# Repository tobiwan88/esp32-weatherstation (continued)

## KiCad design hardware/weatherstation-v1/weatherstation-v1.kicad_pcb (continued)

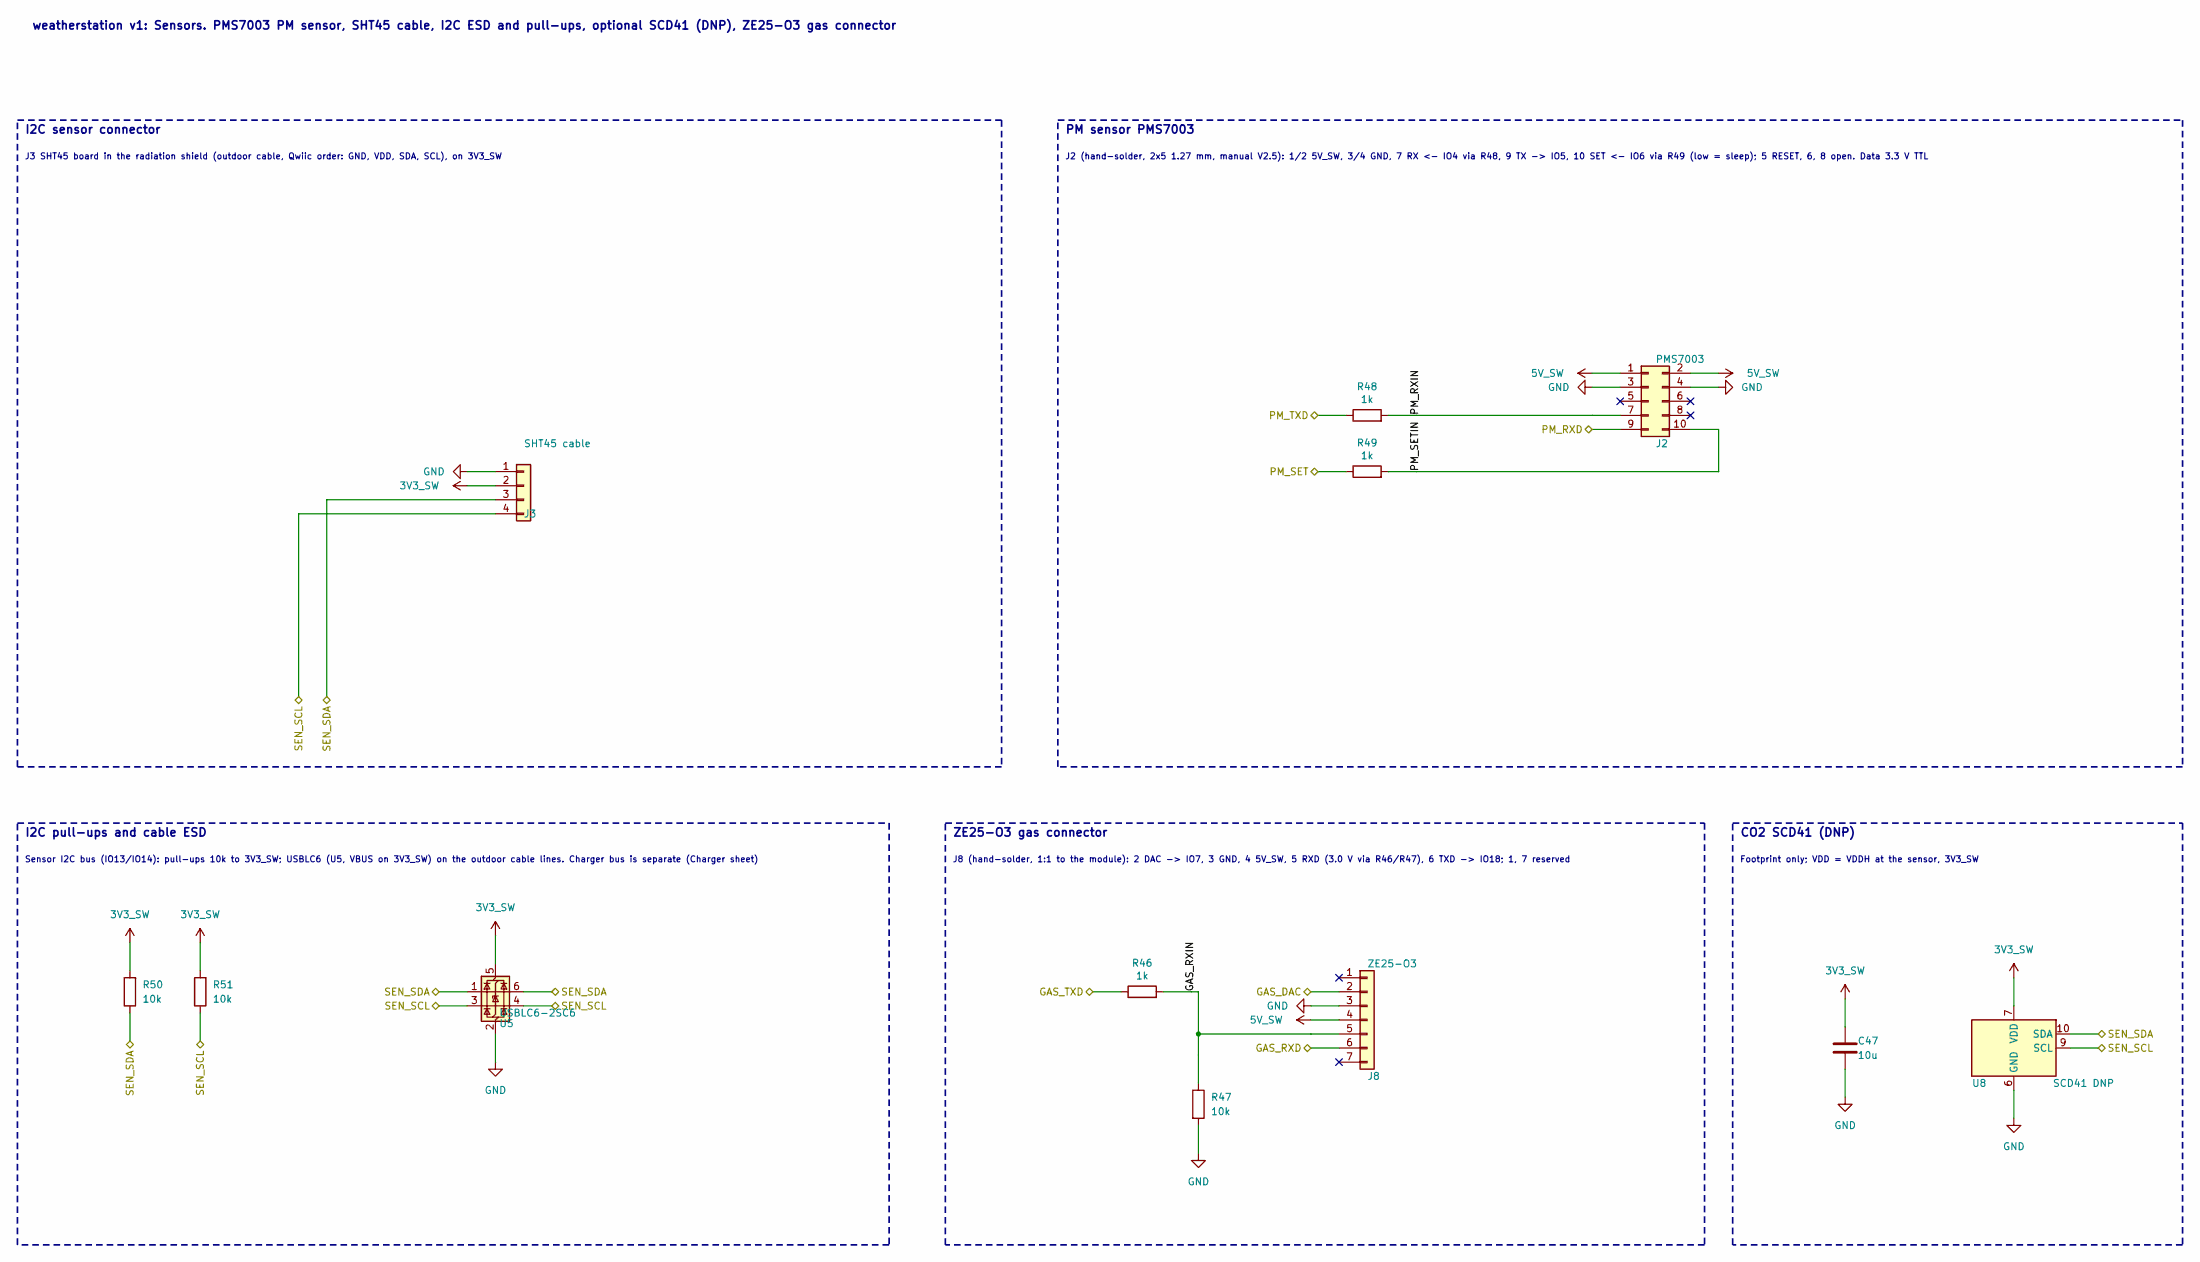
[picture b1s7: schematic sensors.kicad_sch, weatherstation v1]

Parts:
C47: 10u; C_0603_1608Metric; LCSC C19702
J2: PMS7003; PinHeader_2x05_P1.27mm_Vertical
J3: SHT45 cable; JST_SH_SM04B-SRSS-TB_1x04-1MP_P1.00mm_Horizontal; LCSC C160404
J8: ZE25-O3; JST_PH_B7B-PH-K_1x07_P2.00mm_Vertical
R46, R48, R49: 1k; R_0402_1005Metric; LCSC C11702
R47, R50, R51: 10k; R_0402_1005Metric; LCSC C25744
U5: USBLC6-2SC6; SOT-23-6; LCSC C7519
U8: SCD41 DNP; Sensirion_SCD4x-1EP_10.1x10.1mm_P1.25mm_EP4.8x4.8mm

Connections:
3V3_SW: C47.1, J3.2, R50.2, R51.2, U5.5 (VBUS), U8.7 (VDD), U8.19 (VDD); also elsewhere on the board
5V_SW: J2.1, J2.2, J8.4; also elsewhere on the board
/MCU/GAS_DAC: J8.2; also elsewhere on the board
/MCU/GAS_RXD: J8.6; also elsewhere on the board
/MCU/GAS_TXD: R46.1; also elsewhere on the board
/MCU/PM_RXD: J2.9; also elsewhere on the board
/MCU/PM_SET: R49.1; also elsewhere on the board
/MCU/PM_TXD: R48.1; also elsewhere on the board
/MCU/SEN_SCL: J3.4, R51.1, U5.3 (I/O2), U5.4 (I/O2), U8.9 (SCL); also elsewhere on the board
/MCU/SEN_SDA: J3.3, R50.1, U5.1 (I/O1), U5.6 (I/O1), U8.10 (SDA); also elsewhere on the board
/Sensors/GAS_RXIN: J8.5, R46.2, R47.1
/Sensors/PM_RXIN: J2.7, R48.2
/Sensors/PM_SETIN: J2.10, R49.2
GND: C47.2, J2.3, J2.4, J3.1, J8.3, R47.2, U5.2 (GND), U8.6 (GND), U8.20 (GND), U8.21 (GND); also elsewhere on the board

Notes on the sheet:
I2C sensor connector
J3 SHT45 board in the radiation shield (outdoor cable, Qwiic order: GND, VDD, SDA, SCL), on 3V3_SW
PM sensor PMS7003
J2 (hand-solder, 2x5 1.27 mm, manual V2.5): 1/2 5V_SW, 3/4 GND, 7 RX <- IO4 via R48, 9 TX -> IO5, 10 SET <- IO6 via R49 (low = sleep); 5 RESET, 6, 8 open. Data 3.3 V TTL
CO2 SCD41 (DNP)
Footprint only; VDD = VDDH at the sensor, 3V3_SW
I2C pull-ups and cable ESD
Sensor I2C bus (IO13/IO14): pull-ups 10k to 3V3_SW; USBLC6 (U5, VBUS on 3V3_SW) on the outdoor cable lines. Charger bus is separate (Charger sheet)
ZE25-O3 gas connector
J8 (hand-solder, 1:1 to the module): 2 DAC -> IO7, 3 GND, 4 5V_SW, 5 RXD (3.0 V via R46/R47), 6 TXD -> IO18; 1, 7 reserved
weatherstation v1: Sensors. PMS7003 PM sensor, SHT45 cable, I2C ESD and pull-ups, optional SCD41 (DNP), ZE25-O3 gas connector

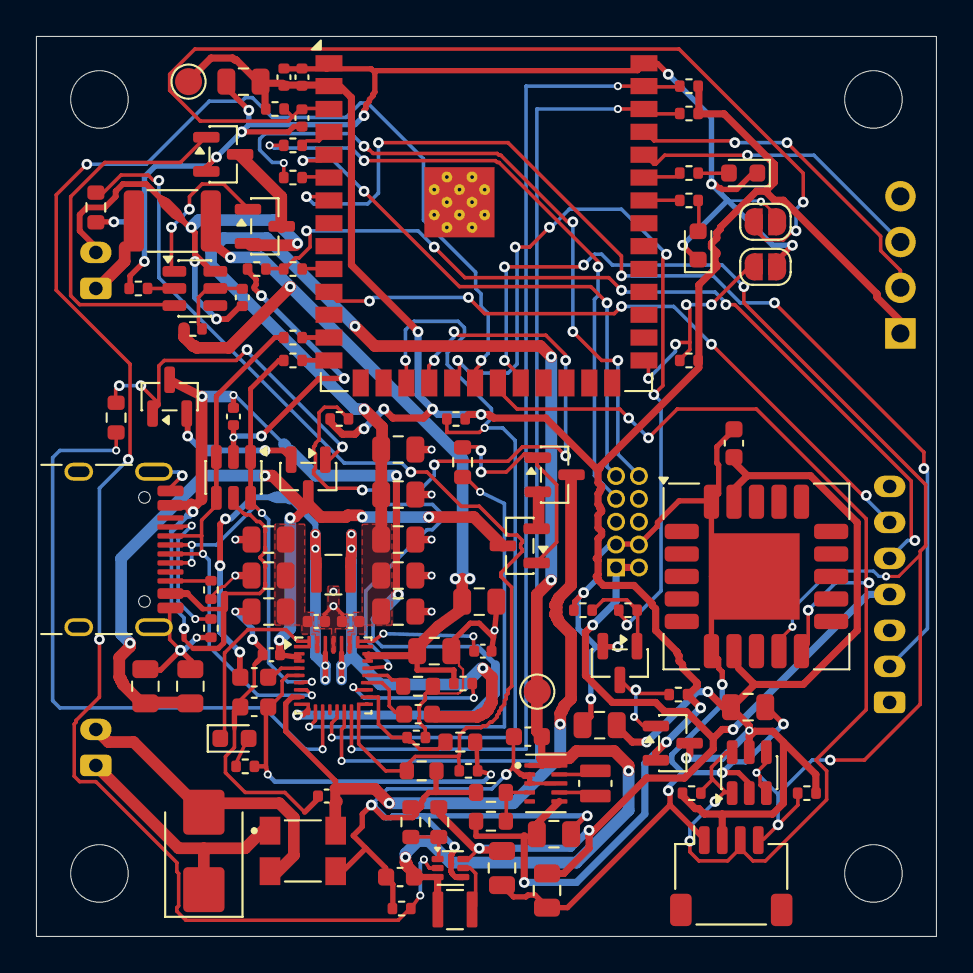
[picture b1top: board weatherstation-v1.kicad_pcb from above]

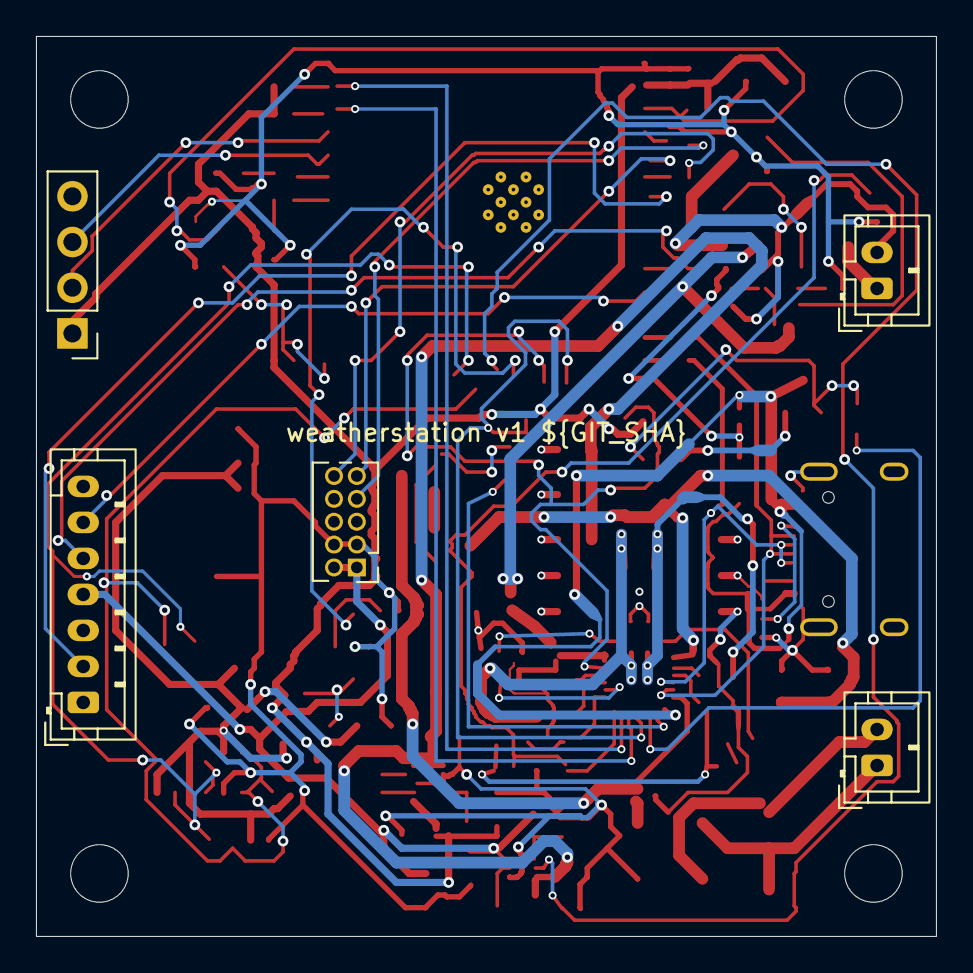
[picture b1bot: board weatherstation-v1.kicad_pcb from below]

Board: 4 copper layers, 50.0 x 50.0 mm, 112 parts (5 on the bottom side), 75 nets.

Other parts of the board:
H1, H2, H3, H4: MountingHole_3.2mm_M3_ISO7380

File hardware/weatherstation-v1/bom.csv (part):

Comment,Designator,Footprint,Quantity,LCSC Part #,Class,Status,Function / notes
USB-C,J1,Connector_USB:USB_C_Receptacle_HRO_TYPE-C-31-M-12,1,C165948,Extended,VERIFIED LCSC part (class and stock 2026-10-31; datasheet values open),
USBLC6-2SC6,"U4,U5",Package_TO_SOT_SMD:SOT-23-6,2,C7519,Extended,VERIFIED LCSC part (class and stock 2026-10-31; datasheet values open),U4: USBLC6-2SC6 (USB); U5: USBLC6-2SC6 (I2C)
5.1k,"R9,R10,R17",Resistor_SMD:R_0402_1005Metric,3,C25905,Basic,VERIFIED LCSC part (class and stock 2026-10-31; datasheet values open),R17: 5.1k (TS top; thresholds about +0.9 C vs 5.24k/30.31k)
AO3400A,"M1,M2,M3,M4,M60,M61",Package_TO_SOT_SMD:SOT-23,6,C20917,Basic,VERIFIED LCSC part (class and stock 2026-10-31; datasheet values open),"M1: AO3400A ACFET1 (N-channel, BQ25798 back-to-back); M2: AO3400A RBFET1 (N-channel, BQ25798 back-to-back); M3: AO3400A ACFET2 (N-channel, BQ25798 back-to-back); M4: AO3400A RBFET2 (N-channel, BQ25798 back-to-back); M60: AO3400A discharge FET (OD); M61: AO3400A charge FET (OC)"
300,"R11,R12",Resistor_SMD:R_0603_1608Metric,2,C23025,Basic,VERIFIED LCSC part (class and stock 2026-10-31; datasheet values open),R11: 300 (candidate; figure 294); R12: 300 (candidate; figure 294)
0.1u,"C1,C2,C6,C9,C13,C31,C60",Capacitor_SMD:C_0402_1005Metric,7,C307331,Basic,VERIFIED LCSC part (class and stock 2026-10-31; datasheet values open),C31: 100n; C60: 0.1u (HY2112 VDD)
SMBJ10A,D1,Diode_SMD:D_SMB,1,C151250,Extended,VERIFIED LCSC part (class and stock 2026-10-31; datasheet values open),"D1: SMBJ10A (PV surge, standoff 10 V, clamp 17 V)"
CMC 90R 3A,L3,weatherstation:CMF4532F_4P,1,C963746,Extended,VERIFIED LCSC part (class and stock 2026-10-31; datasheet values open),L3: CM choke 90 ohm 3 A (CMF4532F-900-2P-T; datasheet page to confirm)
PV IN,J5,Connector_JST:JST_PH_B2B-PH-K_1x02_P2.00mm_Vertical,1,n/a,n/a,HAND-SOLDER,
BQ25798RQMR,U3,Package_DFN_QFN:Texas_RQM0029A_VQFN-29_4x4mm_P0.4mm,1,C2876593,Extended,VERIFIED LCSC part (class and stock 2026-10-31; datasheet values open),
1uH,"L1,L5",weatherstation:L_TDK_VLS252010,2,C88211,Extended,VERIFIED LCSC part (class and stock 2026-10-31; datasheet values open),"L1: 1uH (TDK VLS252010HBX-1R0M-1: Isat 3.22 A, Itemp 2.55 A, 65 mohm max); L5: 1uH (VLS252010HBX-1R0M-1, same as L1)"
PTC 3A,F1,Fuse:Fuse_1812_4532Metric,1,C21004,Extended,VERIFIED LCSC part (class and stock 2026-10-31; datasheet values open),F1: PTC 3 A hold (SMD1812P300TF)
47n,"C3,C4",Capacitor_SMD:C_0603_1608Metric,2,C1622,Basic,VERIFIED LCSC part (class and stock 2026-10-31; datasheet values open),
4.7u,C5,Capacitor_SMD:C_0603_1608Metric,1,C19666,Basic,VERIFIED LCSC part (class and stock 2026-10-31; datasheet values open),
10u,"C7,C8,C10,C11,C12,C14,C15,C16,C17,C18,C19,C20",Capacitor_SMD:C_0805_2012Metric,12,C15850,Basic,VERIFIED LCSC part (class and stock 2026-10-31; datasheet values open),
1n,C21,Capacitor_SMD:C_0402_1005Metric,1,C1523,Basic,VERIFIED LCSC part (class and stock 2026-10-31; datasheet values open),
100,"R13,R60",Resistor_SMD:R_0402_1005Metric,2,C25076,Basic,VERIFIED LCSC part (class and stock 2026-10-31; datasheet values open),R60: 100 (HY2112 VDD)
3.0k,R14,Resistor_SMD:R_0603_1608Metric,1,C4211,Basic,VERIFIED LCSC part (class and stock 2026-10-31; datasheet values open),"R14: 3.0k (PROG: 1S, 1.5 MHz)"
120k,R15,Resistor_SMD:R_0603_1608Metric,1,C25808,Basic,VERIFIED LCSC part (class and stock 2026-10-31; datasheet values open),R15: 120k (ILIM: REGN 5 V x 100/220 = 2.27 V -> 1.59 A clamp)
100k,"R16,R20,R40,R42,R45",Resistor_SMD:R_0402_1005Metric,5,C25741,Basic,VERIFIED LCSC part (class and stock 2026-10-31; datasheet values open),R45: 100k (EN pull-down: boost off by default)
30k,R18,Resistor_SMD:R_0603_1608Metric,1,C22984,Basic,VERIFIED LCSC part (class and stock 2026-10-31; datasheet values open),R18: 30k (TS bottom)
2.2k,R19,Resistor_SMD:R_0402_1005Metric,1,C25879,Basic,VERIFIED LCSC part (class and stock 2026-10-31; datasheet values open),
STAT red,"D2,D10,D11",LED_SMD:LED_0603_1608Metric,3,C2286,Basic,VERIFIED LCSC part (class and stock 2026-10-31; datasheet values open),D10: LED1 red; D11: LED2 red
10k,"R22,R30,R31,R47,R50,R51,R54,R55",Resistor_SMD:R_0402_1005Metric,8,C25744,Basic,VERIFIED LCSC part (class and stock 2026-10-31; datasheet values open),
BATTERY,J6,Connector_JST:JST_PH_B2B-PH-K_1x02_P2.00mm_Vertical,1,n/a,n/a,HAND-SOLDER,
10k NTC,TH1,Resistor_SMD:R_0603_1608Metric,1,C13564,Extended,VERIFIED LCSC part (class and stock 2026-10-31; datasheet values open),"TH1: 10k NTC NCP18XH103F03RB (TS, next to J6)"
HY2112-CB,U6,Package_TO_SOT_SMD:SOT-23-6,1,C168764,Extended,VERIFIED LCSC part (class and stock 2026-10-31; datasheet values open),U6: HY2112-CB LiFePO4 protection
2k,R61,Resistor_SMD:R_0402_1005Metric,1,C4109,Basic,VERIFIED LCSC part (class and stock 2026-10-31; datasheet values open),R61: 2k (HY2112 CS)
ESP32-S3-WROOM-1-N8,U1,RF_Module:ESP32-S3-WROOM-1,1,C2913198,Extended,VERIFIED LCSC part (class and stock 2026-10-31; datasheet values open),
22u,"C30,C41,C42,C43,C45,C46",Capacitor_SMD:C_0805_2012Metric,6,C45783,Basic,VERIFIED LCSC part (class and stock 2026-10-31; datasheet values open),C41: 22u (TPS63802 output: 22 uF per table 10-1); C45: 22u (boost output); C46: 22u (boost output)
1u,"C32,C33",Capacitor_SMD:C_0402_1005Metric,2,C52923,Basic,VERIFIED LCSC part (class and stock 2026-10-31; datasheet values open),
RESET,JP1,Jumper:SolderJumper-2_P1.3mm_Open_RoundedPad1.0x1.5mm,1,n/a,n/a,NOT ASSEMBLED,
BOOT,JP2,Jumper:SolderJumper-2_P1.3mm_Open_RoundedPad1.0x1.5mm,1,n/a,n/a,NOT ASSEMBLED,
22,"R32,R33",Resistor_SMD:R_0402_1005Metric,2,C25092,Basic,VERIFIED LCSC part (class and stock 2026-10-31; datasheet values open),
1k,"R34,R35,R41,R46,R48,R49",Resistor_SMD:R_0402_1005Metric,6,C11702,Basic,VERIFIED LCSC part (class and stock 2026-10-31; datasheet values open),R46: 1k (GAS RXD level: 3.3 V x 10/11 = 3.0 V); R48: 1k (PM RX series); R49: 1k (PM SET series)
DEBUG UART,J7,Connector_PinHeader_2.54mm:PinHeader_1x04_P2.54mm_Vertical,1,n/a,n/a,HAND-SOLDER,
TPS63802,U2,weatherstation:TPS63802_DLA_VSON-HR-10_2x3mm,1,C2845237,Extended,VERIFIED LCSC part (class and stock 2026-10-31; datasheet values open),U2: TPS63802DLA 3.3 V buck-boost
0.47uH,L4,weatherstation:L_Sunlord_WPN201610H,1,C97009,Extended,VERIFIED LCSC part (class and stock 2026-10-31; datasheet values open),"L4: 0.47uH (Sunlord WPN201610HR47MT: Isat 4.0 A max, Irms 2.7 A)"
220k 1%,R52,Resistor_SMD:R_0603_1608Metric,1,C22961,Basic,VERIFIED LCSC part (class and stock 2026-10-31; datasheet values open),R52: 220k 1% (FB top: 0.5 V x (1 + 220k/39k) = 3.32 V)
39k 1%,R53,Resistor_SMD:R_0603_1608Metric,1,C23153,Basic,VERIFIED LCSC part (class and stock 2026-10-31; datasheet values open),"R53: 39k 1% (FB bottom, datasheet max 100k)"
10u,"C40,C44,C47",Capacitor_SMD:C_0603_1608Metric,3,C19702,Basic,VERIFIED LCSC part (class and stock 2026-10-31; datasheet values open),C44: 10u (boost input); C47: 10u (SCD41 VDD)
AO3401A,Q40,Package_TO_SOT_SMD:SOT-23,1,C15127,Basic,VERIFIED LCSC part (class and stock 2026-10-31; datasheet values open),Q40: AO3401A 3V3_SW switch
2N7002,Q41,Package_TO_SOT_SMD:SOT-23,1,C8545,Basic,VERIFIED LCSC part (class and stock 2026-10-31; datasheet values open),Q41: 2N7002 (sensor enable)
TPS61023,U7,Package_TO_SOT_SMD:SOT-563,1,C919459,Extended,VERIFIED LCSC part (class and stock 2026-10-31; datasheet values open),U7: TPS61023DRLR 5 V boost
510k 1%,R43,Resistor_SMD:R_0603_1608Metric,1,C23192,Basic,VERIFIED LCSC part (class and stock 2026-10-31; datasheet values open),R43: 510k 1% (boost FB top: 0.595 V x (1 + 510k/68k) = 5.06 V)
68k 1%,R44,Resistor_SMD:R_0603_1608Metric,1,C23231,Basic,VERIFIED LCSC part (class and stock 2026-10-31; datasheet values open),R44: 68k 1% (boost FB bottom)
PMS7003,J2,Connector_PinHeader_1.27mm:PinHeader_2x05_P1.27mm_Vertical,1,n/a,n/a,HAND-SOLDER,J2: PMS7003 (2x5 1.27 mm)
SCD41 DNP,U8,Sensor:Sensirion_SCD4x-1EP_10.1x10.1mm_P1.25mm_EP4.8x4.8mm,1,n/a,n/a,NOT ASSEMBLED,U8: SCD41 DNP (C3659294)
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
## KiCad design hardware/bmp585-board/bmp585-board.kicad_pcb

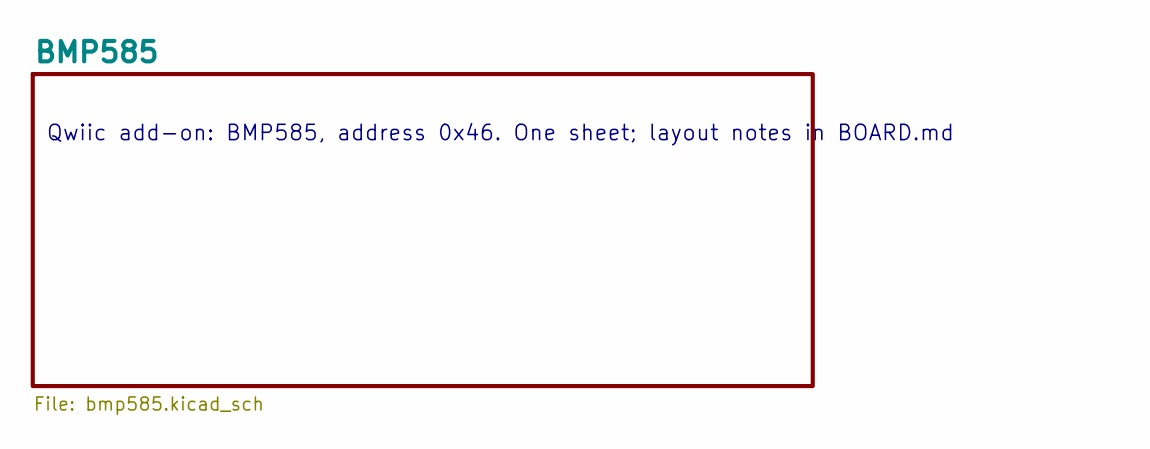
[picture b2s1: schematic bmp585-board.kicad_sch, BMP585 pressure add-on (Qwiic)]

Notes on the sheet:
Qwiic add-on: BMP585, address 0x46. One sheet; layout notes in BOARD.md

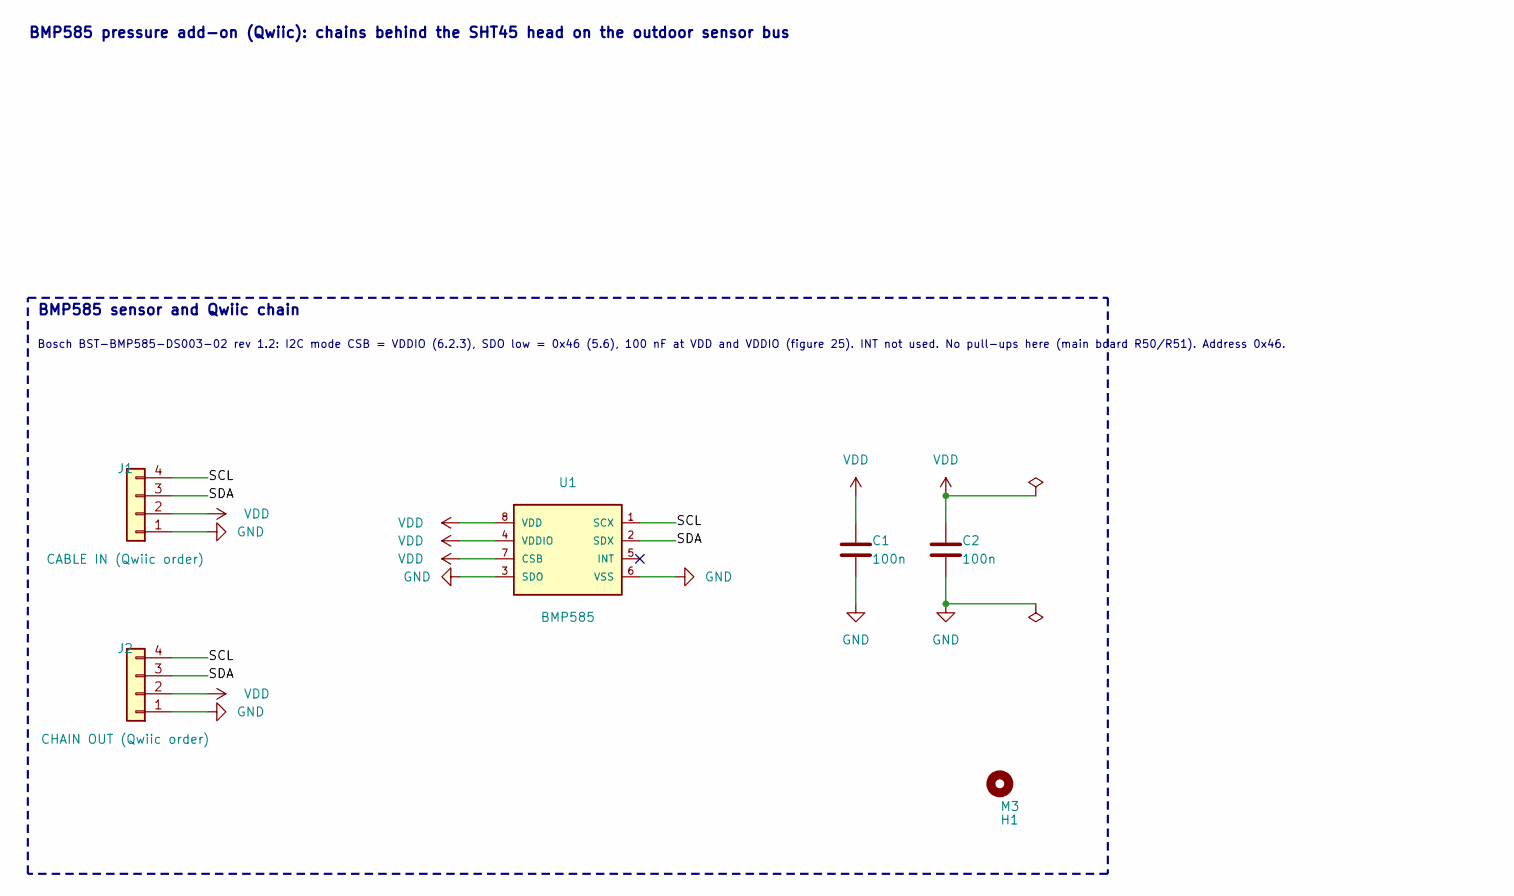
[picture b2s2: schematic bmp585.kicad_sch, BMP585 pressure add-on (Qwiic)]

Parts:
C1, C2: 100n; C_0603_1608Metric; LCSC C14663
H1: M3; MountingHole_3.2mm_M3
J1: CABLE IN (Qwiic order); JST_SH_SM04B-SRSS-TB_1x04-1MP_P1.00mm_Horizontal; LCSC C160404
J2: CHAIN OUT (Qwiic order); JST_SH_SM04B-SRSS-TB_1x04-1MP_P1.00mm_Horizontal; LCSC C160404
U1: BMP585; BMP585_LGA-8_3.25x3.25mm; LCSC C18184976

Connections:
/BMP585/SCL: J1.4, J2.4, U1.1 (SCX)
/BMP585/SDA: J1.3, J2.3, U1.2 (SDX)
GND: C1.2, C2.2, J1.1, J2.1, U1.3 (SDO), U1.6 (VSS)
VDD: C1.1, C2.1, J1.2, J2.2, U1.4 (VDDIO), U1.7 (CSB), U1.8 (VDD)

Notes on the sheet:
BMP585 sensor and Qwiic chain
Bosch BST-BMP585-DS003-02 rev 1.2: I2C mode CSB = VDDIO (6.2.3), SDO low = 0x46 (5.6), 100 nF at VDD and VDDIO (figure 25). INT not used. No pull-ups here (main board R50/R51). Address 0x46.
BMP585 pressure add-on (Qwiic): chains behind the SHT45 head on the outdoor sensor bus

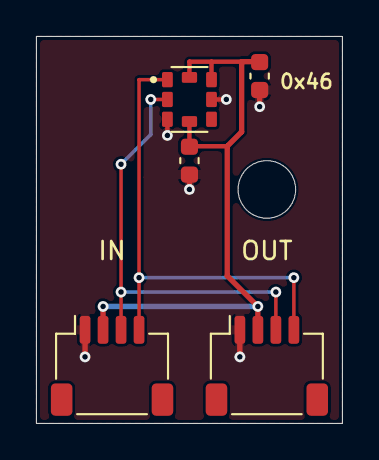
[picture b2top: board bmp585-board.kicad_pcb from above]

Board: 2 copper layers, 17.0 x 21.5 mm, 6 parts (0 on the bottom side), 4 nets.

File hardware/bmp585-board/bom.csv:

Comment,Designator,Footprint,Quantity,LCSC Part #,Class
BMP585,U1,weatherstation:BMP585_LGA-8_3.25x3.25mm,1,C18184976,Extended
100n,C1,Capacitor_SMD:C_0603_1608Metric,1,C14663,Basic
100n,C2,Capacitor_SMD:C_0603_1608Metric,1,C14663,Basic
CABLE IN (Qwiic order),J1,Connector_JST:JST_SH_SM04B-SRSS-TB_1x04-1MP_P1.00mm_Horizontal,1,C160404,Extended
CHAIN OUT (Qwiic order),J2,Connector_JST:JST_SH_SM04B-SRSS-TB_1x04-1MP_P1.00mm_Horizontal,1,C160404,Extended

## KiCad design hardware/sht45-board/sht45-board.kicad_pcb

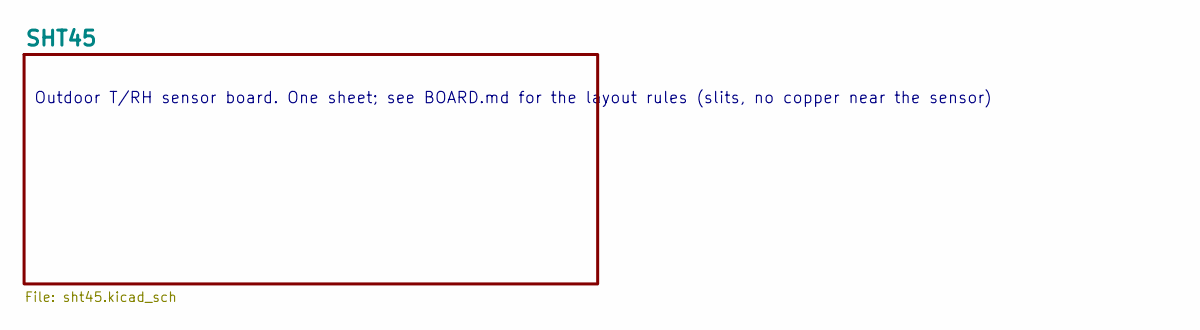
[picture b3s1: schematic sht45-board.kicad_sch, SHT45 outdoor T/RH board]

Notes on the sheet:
Outdoor T/RH sensor board. One sheet; see BOARD.md for the layout rules (slits, no copper near the sensor)

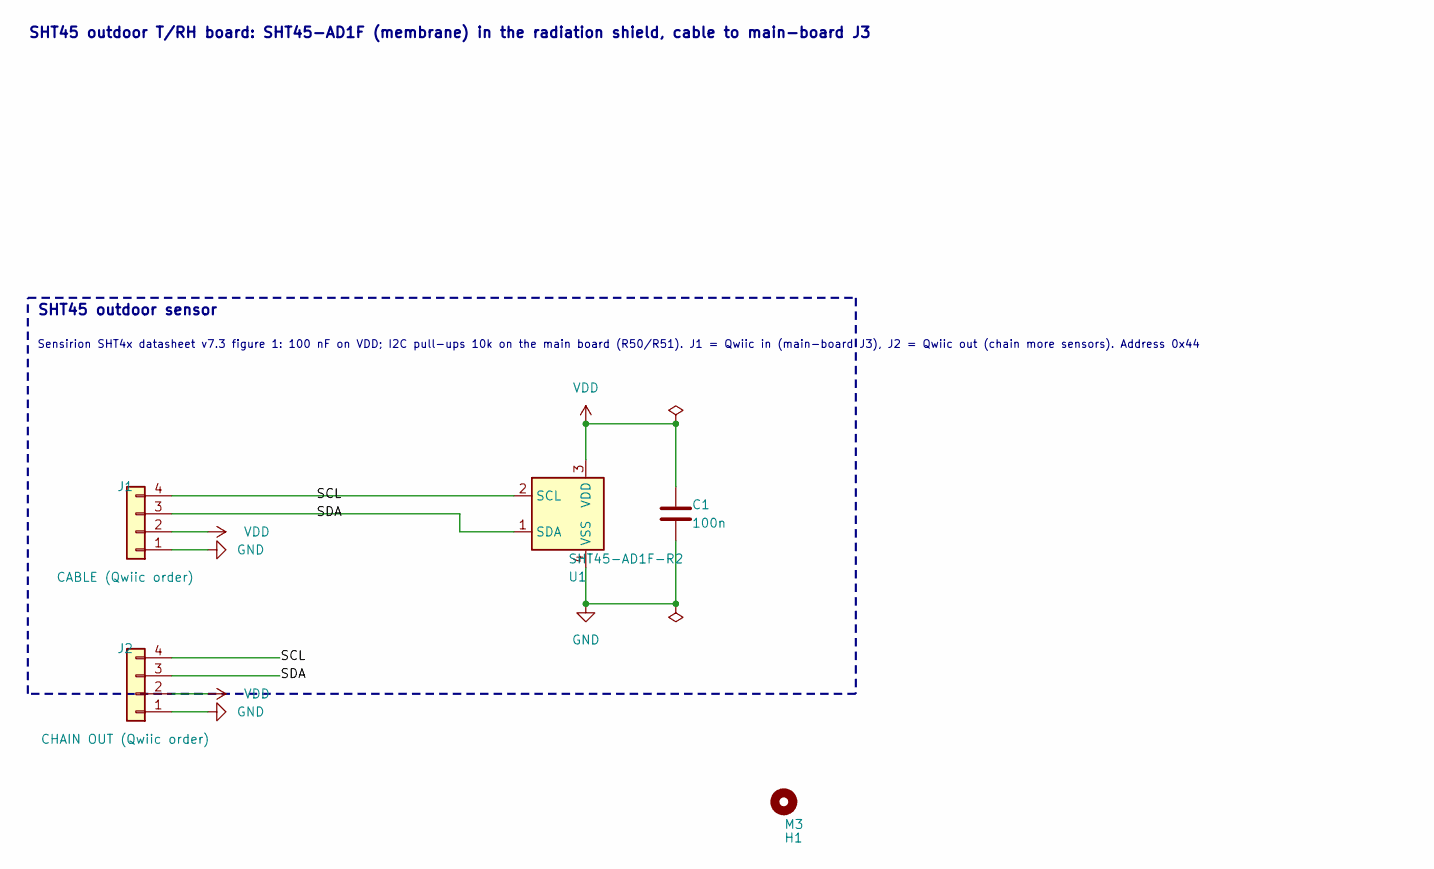
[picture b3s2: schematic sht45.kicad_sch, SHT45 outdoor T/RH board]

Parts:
C1: 100n; C_0603_1608Metric; LCSC C14663
H1: M3; MountingHole_3.2mm_M3
J1: CABLE (Qwiic order); JST_SH_SM04B-SRSS-TB_1x04-1MP_P1.00mm_Horizontal; LCSC C160404
J2: CHAIN OUT (Qwiic order); JST_SH_SM04B-SRSS-TB_1x04-1MP_P1.00mm_Horizontal; LCSC C160404
U1: SHT45-AD1F-R2; Sensirion_DFN-4_1.5x1.5mm_P0.8mm_SHT4x_NoCentralPad; LCSC C5360602

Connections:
/SHT45/SCL: J1.4, J2.4, U1.2 (SCL)
/SHT45/SDA: J1.3, J2.3, U1.1 (SDA)
GND: C1.2, J1.1, J2.1, U1.4 (VSS)
VDD: C1.1, J1.2, J2.2, U1.3 (VDD)

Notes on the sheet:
SHT45 outdoor sensor
Sensirion SHT4x datasheet v7.3 figure 1: 100 nF on VDD; I2C pull-ups 10k on the main board (R50/R51). J1 = Qwiic in (main-board J3), J2 = Qwiic out (chain more sensors). Address 0x44
SHT45 outdoor T/RH board: SHT45-AD1F (membrane) in the radiation shield, cable to main-board J3

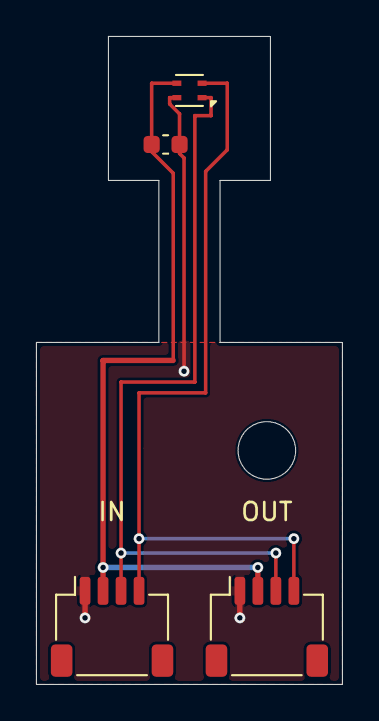
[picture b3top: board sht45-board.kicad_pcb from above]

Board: 2 copper layers, 17.0 x 36.0 mm, 5 parts (0 on the bottom side), 4 nets.

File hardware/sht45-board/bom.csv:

Comment,Designator,Footprint,Quantity,LCSC Part #,Class
SHT45-AD1F-R2,U1,Sensor_Humidity:Sensirion_DFN-4_1.5x1.5mm_P0.8mm_SHT4x_NoCentralPad,1,C5360602,Extended
100n,C1,Capacitor_SMD:C_0603_1608Metric,1,C14663,Basic
CABLE (Qwiic order),J1,Connector_JST:JST_SH_SM04B-SRSS-TB_1x04-1MP_P1.00mm_Horizontal,1,C160404,Extended
CHAIN OUT (Qwiic order),J2,Connector_JST:JST_SH_SM04B-SRSS-TB_1x04-1MP_P1.00mm_Horizontal,1,C160404,Extended

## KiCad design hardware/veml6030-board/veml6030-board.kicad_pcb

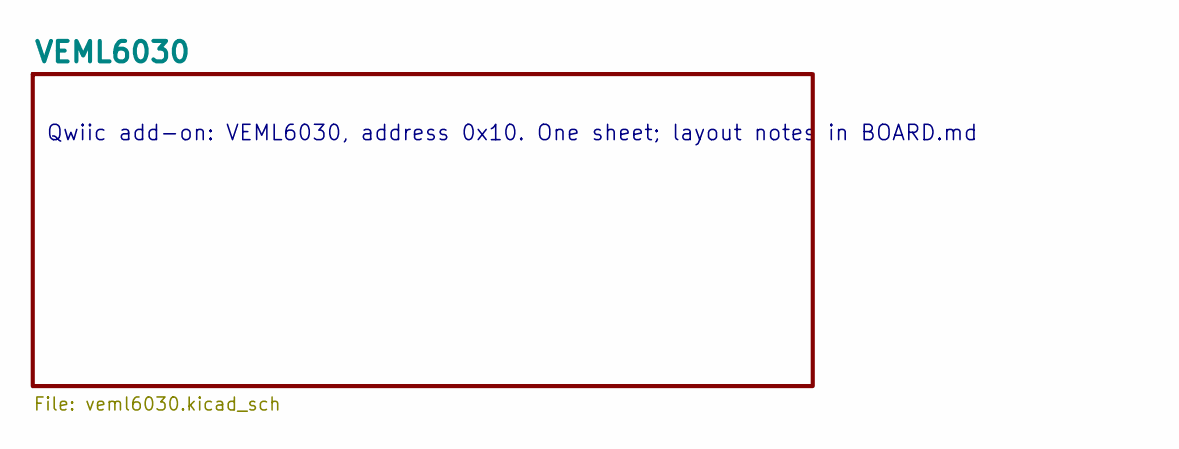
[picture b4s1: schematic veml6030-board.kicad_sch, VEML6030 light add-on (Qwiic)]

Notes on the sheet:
Qwiic add-on: VEML6030, address 0x10. One sheet; layout notes in BOARD.md

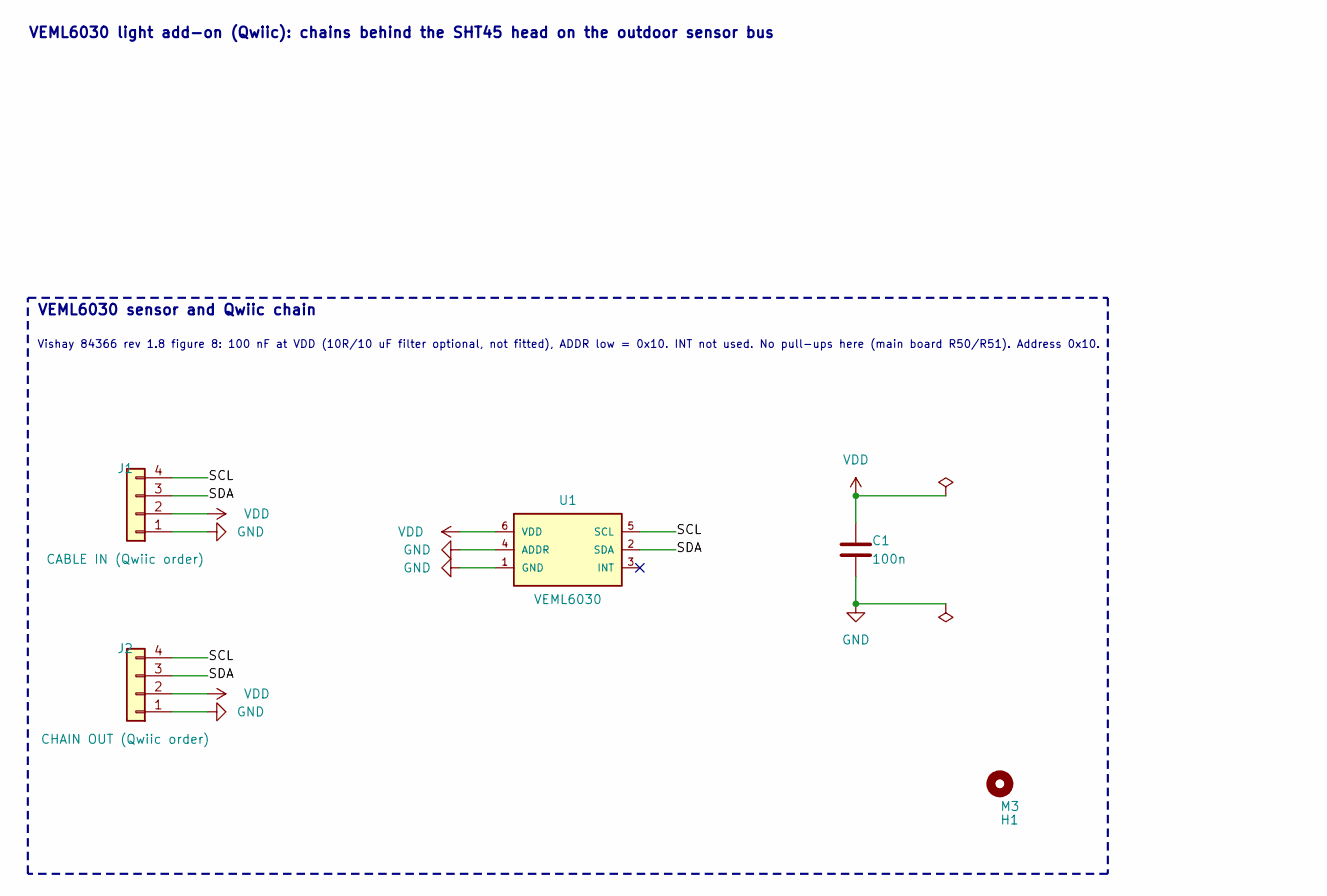
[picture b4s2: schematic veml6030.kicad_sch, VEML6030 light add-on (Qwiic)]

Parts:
C1: 100n; C_0603_1608Metric; LCSC C14663
H1: M3; MountingHole_3.2mm_M3
J1: CABLE IN (Qwiic order); JST_SH_SM04B-SRSS-TB_1x04-1MP_P1.00mm_Horizontal; LCSC C160404
J2: CHAIN OUT (Qwiic order); JST_SH_SM04B-SRSS-TB_1x04-1MP_P1.00mm_Horizontal; LCSC C160404
U1: VEML6030; Vishay_VEML6030_2x2mm; LCSC C132182

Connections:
/VEML6030/SCL: J1.4, J2.4, U1.5 (SCL)
/VEML6030/SDA: J1.3, J2.3, U1.2 (SDA)
GND: C1.2, J1.1, J2.1, U1.1 (GND), U1.4 (ADDR)
VDD: C1.1, J1.2, J2.2, U1.6 (VDD)

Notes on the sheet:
VEML6030 sensor and Qwiic chain
Vishay 84366 rev 1.8 figure 8: 100 nF at VDD (10R/10 uF filter optional, not fitted), ADDR low = 0x10. INT not used. No pull-ups here (main board R50/R51). Address 0x10.
VEML6030 light add-on (Qwiic): chains behind the SHT45 head on the outdoor sensor bus

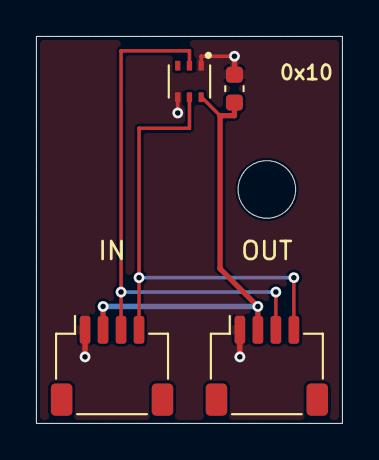
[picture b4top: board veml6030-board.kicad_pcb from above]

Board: 2 copper layers, 17.0 x 21.5 mm, 5 parts (0 on the bottom side), 4 nets.

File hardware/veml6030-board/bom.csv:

Comment,Designator,Footprint,Quantity,LCSC Part #,Class
VEML6030,U1,weatherstation:Vishay_VEML6030_2x2mm,1,C132182,Extended
100n,C1,Capacitor_SMD:C_0603_1608Metric,1,C14663,Basic
CABLE IN (Qwiic order),J1,Connector_JST:JST_SH_SM04B-SRSS-TB_1x04-1MP_P1.00mm_Horizontal,1,C160404,Extended
CHAIN OUT (Qwiic order),J2,Connector_JST:JST_SH_SM04B-SRSS-TB_1x04-1MP_P1.00mm_Horizontal,1,C160404,Extended

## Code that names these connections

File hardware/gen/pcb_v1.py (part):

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    "H1": (3.5, 3.5, 0), "H2": (W - 3.5, 3.5, 0), "H3": (3.5, H - 3.5, 0), "H4": (W - 3.5, H - 3.5, 0),
    # battery: cell connector on the left edge, NTC beside it
    "J6": (3.3, 14.0, 270, "B"), "U6": (8.8, 14.0, 0),
    # pinned 2026-11-03 at their NEAR positions (the BAT_PACK trunk lands next to F1.2 and M60)
    "F1": (7.55, 10.25, 0), "M60": (12.688, 10.55, 0), "C60": (11.438, 14.5, -90), "R60": (8.688, 16.25, 0),
    # debug corner
    "J7": (48.0, 16.5, 0, "B"), "JP1": (40.5, 10.3, 0), "JP2": (40.5, 12.8, 0),  # tweezer pads
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         if not r.startswith("H") and r != "U1" else p for r, p in FIXED.items()}

# BQ25798 power stage drawn by hand (SLUSDV2C 8.4.1/8.4.2, priority order): 0402 PMID and SYS caps on top of the
# PMID-SW1-GND-SW2-SYS pin row sharing the GND pin; SW1/SW2 drop through vias under the IC to B.Cu and come back up at
# the inductor above the caps; bulk caps in a column beside each, joined by F.Cu pours. Offsets from U3's centre (mm).
CHARGER = {
    "C9": (-0.95, -3.0, 0), "C13": (0.95, -3.0, 180), "L1": (0.0, -5.6, 0),
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    "C14": (3.6, -3.55, 0), "C15": (3.6, -5.55, 0), "C16": (3.6, -7.55, 0), "C17": (3.6, -10.05, 0), "C20": (8.1, -4.1, 0),
    "C18": (3.6, -12.55, 0),
    # small parts, one ring around the pins in pin order so every pin fans out without crossing (items 3-5, 7):
    # right: BAT cap beside the BAT pins, then PROG, BTST2, ILIM, TS rows; BATP sense and SDRV cap further out
    "C19": (5.6, -1.35, 0), "C21": (8.3, -1.35, 0), "R14": (4.7, 0.6, 0), "R13": (7.2, 0.45, 0),
    "C4": (4.7, 2.15, 0), "R16": (4.6, 3.45, 0), "R15": (7.05, 3.7, 180), "R18": (4.9, 5.3, 0), "R17": (7.5, 5.3, 180),
    # left: VBUS 100 nF at the VBUS pins, BTST1 cap, REGN cap (2 GND vias to the plane, item 3)
    "C6": (-3.45, -1.15, 180), "C3": (-4.4, 0.1, 180), "C5": (-4.4, 1.75, 180),
    # ACFET1/RBFET1 output FET M2: its VBUS pin at the top of the hand-drawn VBUS channel
    "M2": (-1.4, -11.05, -90),
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             (_DP, 15.3, 35.85), (_DN, 15.3, 36.6), (_DN, 9.25, 28.745), ("GND", 8.9, 33.4)],
}
# Charge trunks at class width, absolute board mm (the autorouter necks these down to 0.2 mm in the crowded middle):
# BAT_PACK from the bulk cap C20 on B.Cu diagonally under U1's pin column to two 0.6/0.3 vias, up to the fuse F1;
# USB_VBUS from J1's A4/B9 pad right of the shell keepout, between M1 and U4, to M1's source.
TRUNKS = {"pours": [], "tracks": [
    ("BAT_PACK", "F", 0.5, [(23.275, 30.125), (24.075, 30.125)]), ("BAT_PACK", "F", 0.65, [(23.655, 30.125), (23.655, 30.9)]),
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    return [(-x, y) for x, y in pts]


# bottom edge raised to -2.8 left of x -1.75 (still covers the C10/C14 pads): a channel above the pin row for STAT
# (left) and SDRV (right, mirrored SYS pour)
_PMID = [(-1.0, -1.3), (-0.8, -1.3), (-0.8, -2.45), (-1.1, -2.45), (-1.1, -3.5), (-1.6, -3.5), (-1.6, -8.4),
         (-3.25, -8.4), (-3.25, -2.8), (-1.75, -2.8), (-1.75, -2.3), (-1.0, -2.3)]
_SW1_B = [(-0.45, 0.25), (-0.45, -0.55), (-1.0, -1.1), (-1.0, -7.85)]
# U3 bottom row (net, pin x, bend y, via x): ACDRV2, ACDRV1, CE, SCL, SDA, TS (pin 12 QON unused)
_FAN = [("/Charger/ACDRV2", -1.0, 2.7, -1.1), ("/Charger/ACDRV1", -0.6, 2.6, -0.3), ("/Charger/CHG_CE", 0.2, 2.6, 0.5),
        ("/Charger/CHG_SCL", 0.6, 2.5, 1.3), ("/Charger/CHG_SDA", 1.0, 2.4, 2.1), ("/Battery/TS", 1.85, 2.6, 2.9)]
# off by default: trial 7 (2026-11-03) closed the bottom-row nets but the via row cut the channel under U3 (10 open
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        ("VBUS", "F", 0.4, [(-3.0, -1.95), (-2.97, -1.3)]), ("VBUS", "F", 0.3, [(-2.97, -1.15), (-1.9, -1.0)]),
        ("VBUS", "B", 0.65, [(-3.0, -1.95), (-2.4, -2.6)]), ("VBUS", "B", 0.65, [(-2.4, -2.6), (-2.4, -8.75)]),
        ("VBUS", "F", 0.5, [(-2.4, -8.75), (-2.1, -8.75), (-1.4, -9.45)]),  # one 0.6/0.3 via (KRT drops parallel-via links)
        # STAT (top-left corner pin) left above C6 in the pour channel, down beside C3/C5 to the debug LED D2
        # (pins 1 and 24 are L-shaped corner pads open toward the corner: the stubs leave through that notch)
        ("/Charger/STAT", "F", 0.2, [(-1.38, -1.9), (-2.0, -1.9), (-2.65, -2.55), (-4.75, -2.55), (-6.05, -1.25),
                                     (-6.05, 3.1), (-6.29, 3.5)]),
        # SDRV (top-right corner pin) right in the SYS pour channel, above C19, down to its 1 nF C21
        # left pins in one fan: BTST1 and REGN to their caps, VAC2 (PV_IN sense, uA) between pins 7 and 9 at the
        # 0.3 mm charge-class floor (0.15 mm each side), down past the REGN cap to C2
        ("/Charger/BTST1", "F", 0.2, [(-1.9, -0.4), (-2.9, -0.4), (-3.3, 0.0)]),
        ("REGN", "F", 0.2, [(-1.9, 0.0), (-2.55, 0.0), (-2.85, 0.3), (-2.85, 1.05), (-3.3, 1.5)]),
        ("/Charger/PV_IN", "F", 0.3, [(-1.9, 1.2), (-2.3, 1.2), (-2.65, 1.55), (-2.65, 3.1), (0.11, 5.86), (0.11, 6.45)]),
        # right column in pin order (no crossings): PROG into R14's upper pad half, BTST2 down to C4, BATP through a
        # via under the body (clear of the SW2 vias) and B.Cu to R13, ILIM down to R16, TS from the corner pad's
        # inner arm down to R18, INT to a via for its long run to the MCU; BAT pins to the BAT cap at 0.4 mm
        ("/Charger/PROG", "F", 0.2, [(1.9, 0.0), (3.0, 0.0), (3.25, 0.25), (3.5, 0.25)]),
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        ("/Battery/TS", "F", 0.2, [(1.4, 2.0), (1.4, 3.8), (2.9, 5.3), (4.0, 5.3)]),
        ("/Charger/CHG_INT", "F", 0.2, [(1.9, -0.4), (3.05, -0.5)]),
        ("BAT_PACK", "F", 0.4, [(1.9, -1.1), (4.4, -1.1)]),
        ("BAT_PACK", "F", 0.3, [(1.95, -1.2), (1.95, -0.85)]),  # BAT pins 23 and 22 joined at 0.3 mm
        # BATP sense resistor R13 to the BAT cap C19, under C19's GND pad
        ("BAT_PACK", "F", 0.3, [(6.69, 0.45), (6.69, -0.3), (4.65, -0.3), (4.65, -0.8)]),
        ("/Charger/SDRV", "F", 0.2, [(1.35, -1.9), (2.2, -1.9), (2.775, -2.325)]),
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                    taken.append((ox + min(x1, x2) - g, oy + min(y1, y2) - g, ox + max(x1, x2) + g, oy + max(y1, y2) + g))
        for net, x, y, *_ in copper["vias"]:
            taken.append((ox + x - 0.45, oy + y - 0.45, ox + x + 0.45, oy + y + 0.45))
    # escape bands for U3's signal pins (TS/ILIM/BATP/BTST2/PROG/INT on the right below BAT, the bottom row, D+/D-/
    # PV_IN on the left below REGN): no part there, so every pin can fan out before the router takes over
    for bx0, by0, bx1, by1 in ((2.4, -0.55, 4.3, 2.7), (-2.7, 2.4, 2.7, 4.3), (-4.3, 0.25, -2.4, 2.7)):
        taken.append((ux3 + bx0, uy3 + by0, ux3 + bx1, uy3 + by1))

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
